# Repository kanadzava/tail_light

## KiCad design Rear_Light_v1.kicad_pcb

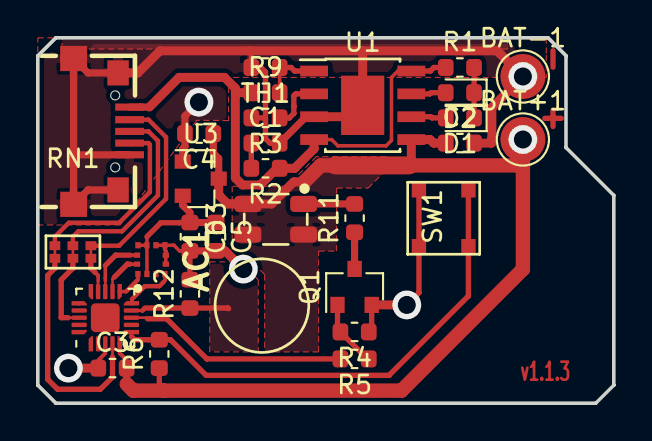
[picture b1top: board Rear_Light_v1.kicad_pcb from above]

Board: 2 copper layers, 32.0 x 20.3 mm, 29 parts (0 on the bottom side), 23 nets.

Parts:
AC1: LIS2DH12TR; PQFN50P200X200X100-12N
BAT+1: BAT+; TestPoint_Pad_D2.5mm
BAT-1: BAT-; TestPoint_Pad_D2.5mm
C1, C2, C4, C5: 10u; C_0603_1608Metric
C3, C6: 100n; C_0603_1608Metric
D1: green; LED_0603_1608Metric
D2: red; LED_0603_1608Metric
D3: LED; Wurth_WL-SMTD
J1: USB_B_Micro; Korean Hroparts Elec U-F-M5SS-W-1
Q1: si2302; SOT-23
R1, R5, R6: 1k; R_0603_1608Metric
R2: 1R; R_0603_1608Metric
R3: 10k; R_0603_1608Metric
R4: 100k; R_0603_1608Metric
R9: 22k; R_0603_1608Metric
R11: 33R; R_0603_1608Metric
R12: 1M; R_0603_1608Metric
RN1: R_Pack03; SolderJumper_3pin_small_P1.0mm
SW1: SW_Push; GANGYUAN KAN3742-035B020
TH1: Thermistor_NTC 47k B>=4100; R_0603_1608Metric
U1: TP4056; SOP-8-PP_3.9x4.9mm_P1.27mm
U2: N76E003AQ20; QFN-20-1EP_3x3mm_P0.40mm_EP1.65x1.65mm_nuvoton_ground_pad
U3: SC662K; SOT-23

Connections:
+3V3: AC1.2, AC1.9, AC1.10, C5.1, C6.1, U3.2
/+5v: J1.1, R1.1, R2.1, R9.1, U1.4, U1.8
/ICPCLK: J1.2, RN1.1, RN1.6, U2.14
/ICPDA: J1.4, RN1.3, RN1.4, U2.4
/INT1: AC1.12, U2.12
/INT2: AC1.11, U2.13
/LED_STDBY: D1.2, U1.6
/LED_chrg: D2.2, U1.7
/LED_gate: R5.2, U2.8
/RST: J1.3, RN1.2, RN1.5, U2.18
/SCL: AC1.1, U2.11
/SDA: AC1.4, U2.10
/bat+: BAT+1.1, C2.1, C3.2, C4.1, D3.1, R6.1, U1.5, U2.5, U3.3
/button: R6.2, SW1.2, U2.6
/light(analog): R12.1, U2.9
/prog: R3.1, U1.2
GND: AC1.5, AC1.6, AC1.7, AC1.8, BAT-1.1, C1.2, C2.2, C3.1, C4.2, C5.2, C6.2, J1.5, J1.6, J1.7, J1.8, J1.9, Q1.2, R3.2, R4.1, R12.2, SW1.1, TH1.2, U1.3, U1.9, U2.3, U3.1
unnamed: C1.1, R2.2
unnamed: D1.1, D2.1, R1.2
unnamed: D3.2, R11.2
unnamed: Q1.1, R4.2, R5.1
unnamed: Q1.3, R11.1
unnamed: R9.2, TH1.1, U1.1

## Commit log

2019-10-22 added silicone mold view and .step
2019-11-03 chematic + pcb added
